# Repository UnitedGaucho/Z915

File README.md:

# Z915

An nRF52840 (MDBT50Q) wireless mechanical keyboard that fits in the chassis and recreates the functions of the Logitech G915. ZMK is used as the firmware.
G915 features to be recreated
  - Per-key RGB LED
  - Volume scroll wheel
  - Wireless (BLE)
  - Battery level reporting

Features to be added/upgraded
  - USB-C charging (G915 has micro-B USB)
  - Upgrade the feel of the rubber dome switches by using snap dome switches underneath the rubber
  - ZMK-included features

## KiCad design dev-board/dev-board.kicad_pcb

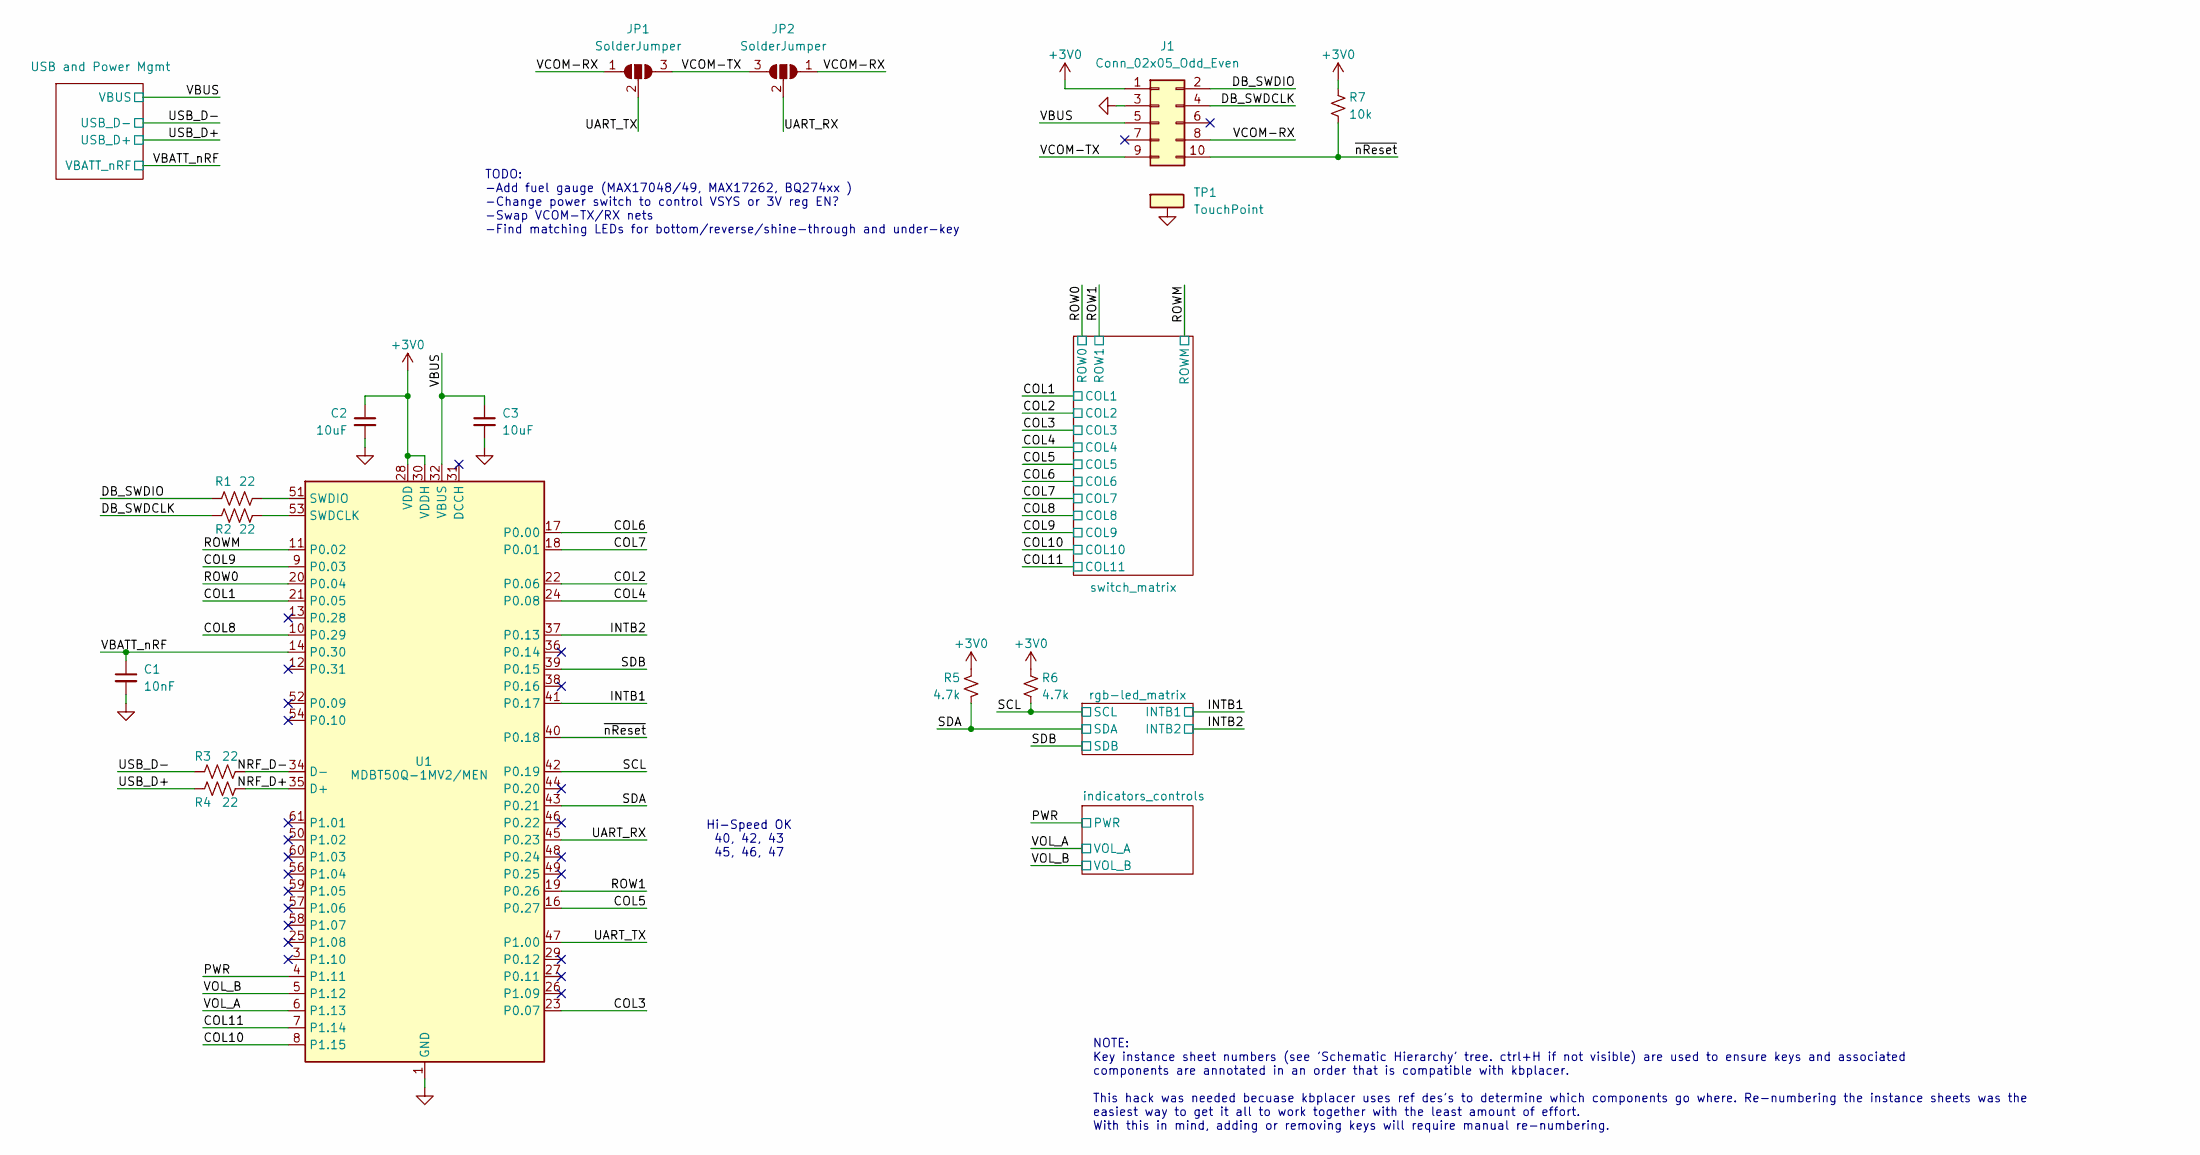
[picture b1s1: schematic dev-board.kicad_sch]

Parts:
C1: 10nF; C_0603_1608Metric
C2, C3: 10uF; C_1206_3216Metric
J1: Conn_02x05_Odd_Even; Tag-Connect_TC2050-IDC-FP_2x05_P1.27mm_Vertical
JP1, JP2: SolderJumper; SolderJumper-3_P1.3mm_Open_RoundedPad1.0x1.5mm
R1, R2, R3, R4: 22; R_0402_1005Metric
R5, R6: 4.7k; R_0402_1005Metric
R7: 10k; R_0402_1005Metric
TP1: TouchPoint; TestPoint_Pad_4.0x4.0mm
U1: MDBT50Q-1MV2/MEN; Raytac_MDBT50Q

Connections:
+3V0: C2.1, J1.1, R5.2, R6.2, R7.2, U1.28 (VDD), U1.30 (VDDH); also elsewhere on the board
/COL1: U1.21 (P0.05); also elsewhere on the board
/COL2: U1.22 (P0.06); also elsewhere on the board
/COL3: U1.23 (P0.07); also elsewhere on the board
/COL4: U1.24 (P0.08); also elsewhere on the board
/COL5: U1.16 (P0.27); also elsewhere on the board
/COL6: U1.17 (P0.00); also elsewhere on the board
/COL7: U1.18 (P0.01); also elsewhere on the board
/COL8: U1.10 (P0.29); also elsewhere on the board
/COL9: U1.9 (P0.03); also elsewhere on the board
/COL10: U1.8 (P1.15); also elsewhere on the board
/COL11: U1.7 (P1.14); also elsewhere on the board
/DB_SWDCLK: J1.4, R2.1
/DB_SWDIO: J1.2, R1.1
/INTB1: U1.41 (P0.17); also elsewhere on the board
/INTB2: U1.37 (P0.13); also elsewhere on the board
/NRF_D+: R4.2, U1.35 (D+)
/NRF_D-: R3.2, U1.34 (D-)
/PWR: U1.4 (P1.11); also elsewhere on the board
/ROW0: U1.20 (P0.04); also elsewhere on the board
/ROW1: U1.19 (P0.26); also elsewhere on the board
/ROWM: U1.11 (P0.02); also elsewhere on the board
/SCL: R6.1, U1.42 (P0.19); also elsewhere on the board
/SDA: R5.1, U1.43 (P0.21); also elsewhere on the board
/SDB: U1.39 (P0.15); also elsewhere on the board
/UART_RX: JP2.2 (C), U1.45 (P0.23)
/UART_TX: JP1.2 (C), U1.47 (P1.00)
/USB_D+: R4.1; also elsewhere on the board
/USB_D-: R3.1; also elsewhere on the board
/VBATT_nRF: C1.1, U1.14 (P0.30); also elsewhere on the board
/VBUS: C3.1, J1.5, U1.32 (VBUS); also elsewhere on the board
/VCOM-RX: J1.8, JP1.1 (A), JP2.1 (A)
/VCOM-TX: J1.9, JP1.3 (B), JP2.3 (B)
/VOL_A: U1.6 (P1.13); also elsewhere on the board
/VOL_B: U1.5 (P1.12); also elsewhere on the board
/~nReset: J1.10, R7.1, U1.40 (P0.18)
GND: C1.2, C2.2, C3.2, J1.3, TP1.1, U1.1 (GND), U1.2 (GND), U1.15 (GND), U1.33 (GND), U1.55 (GND); also elsewhere on the board
unnamed: R2.2, U1.53 (SWDCLK)
unnamed: R1.2, U1.51 (SWDIO)

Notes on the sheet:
NOTE: Key instance sheet numbers (see 'Schematic Hierarchy' tree. ctrl+H if not visible) are used to ensure keys and associated components are annotated in an order that is compatible with kbplacer. This hack was needed becuase kbplacer uses ref des's to determine which components go where. Re-numb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
Hi-Speed OK 40, 42, 43 45, 46, 47
TODO: -Add fuel gauge (MAX17048/49, MAX17262, BQ274xx ) -Change power switch to control VSYS or 3V reg EN? -Swap VCOM-TX/RX nets -Find matching LEDs for bottom/reverse/shine-through and under-key

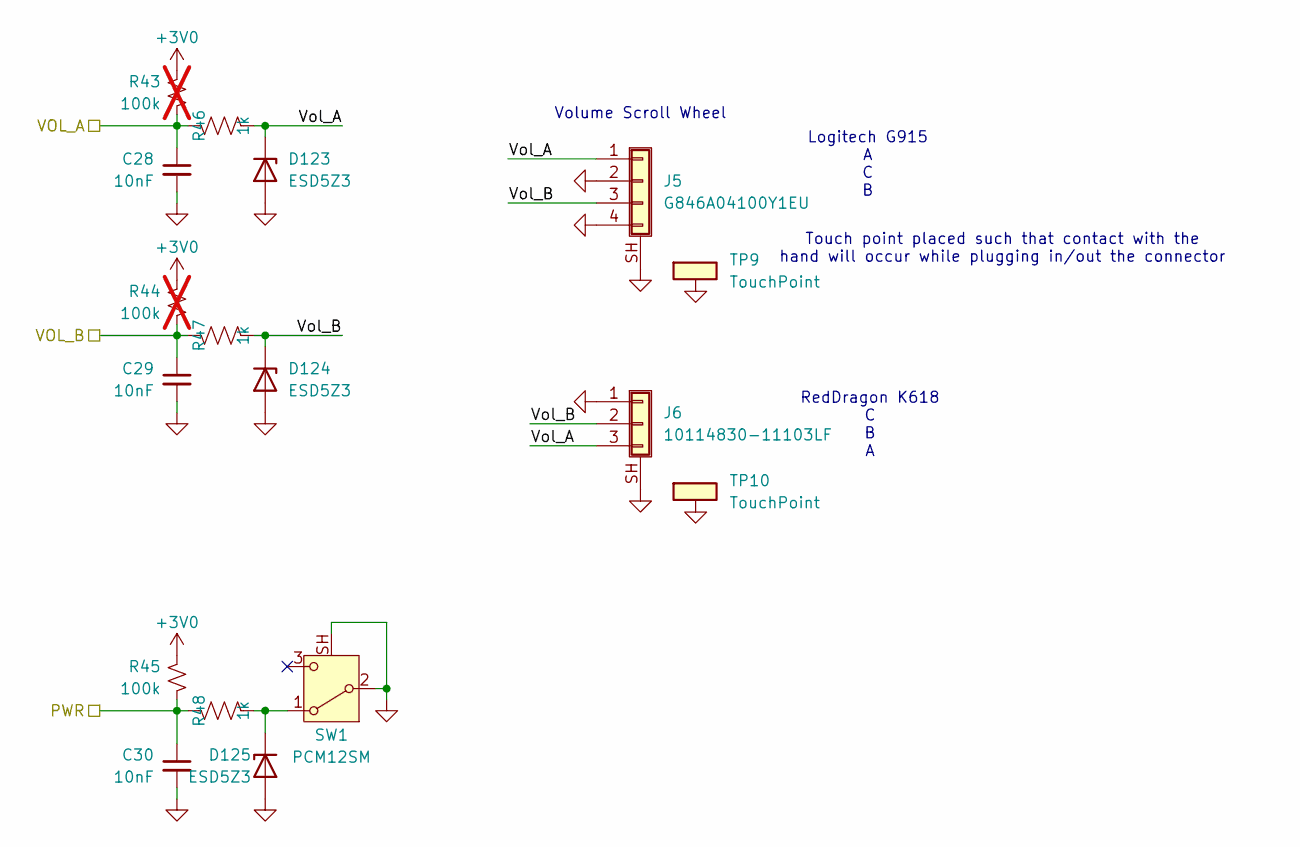
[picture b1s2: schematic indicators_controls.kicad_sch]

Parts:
C28, C29, C30: 10nF; C_0603_1608Metric
D123, D124, D125: ESD5Z3; D_SOD-523
J5: G846A04100Y1EU; AMPHENOL_G846A04100Y1EU
J6: 10114830-11103LF; AMPHENOL_10114830-11103LF
R43, R44: 100k; R_0402_1005Metric; not fitted
R45: 100k; R_0402_1005Metric
R46, R47, R48: 1k; R_0402_1005Metric
SW1: PCM12SM; SW_PCM12SMTR
TP9, TP10: TouchPoint; TestPoint_Pad_4.0x4.0mm

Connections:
+3V0: R43.2, R44.2, R45.2; also elsewhere on the board
/PWR: C30.1, R45.1, R48.1; also elsewhere on the board
/VOL_A: C28.1, R43.1, R46.1; also elsewhere on the board
/VOL_B: C29.1, R44.1, R47.1; also elsewhere on the board
/indicators_controls/Vol_A: D123.1 (K), J5.1, J6.3, R46.2
/indicators_controls/Vol_B: D124.1 (K), J5.3, J6.2, R47.2
GND: C28.2, C29.2, C30.2, D123.2 (A), D124.2 (A), D125.2 (A), J5.2, J5.4, J5.SH (Shield), J6.1, J6.SH (Shield), SW1.2 (B), SW1.SH, TP9.1, TP10.1; also elsewhere on the board
unnamed: D125.1 (K), R48.2, SW1.1 (A)

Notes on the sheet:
Logitech G915 A C B
Touch point placed such that contact with the hand will occur while plugging in/out the connector
RedDragon K618 C B A
Volume Scroll Wheel

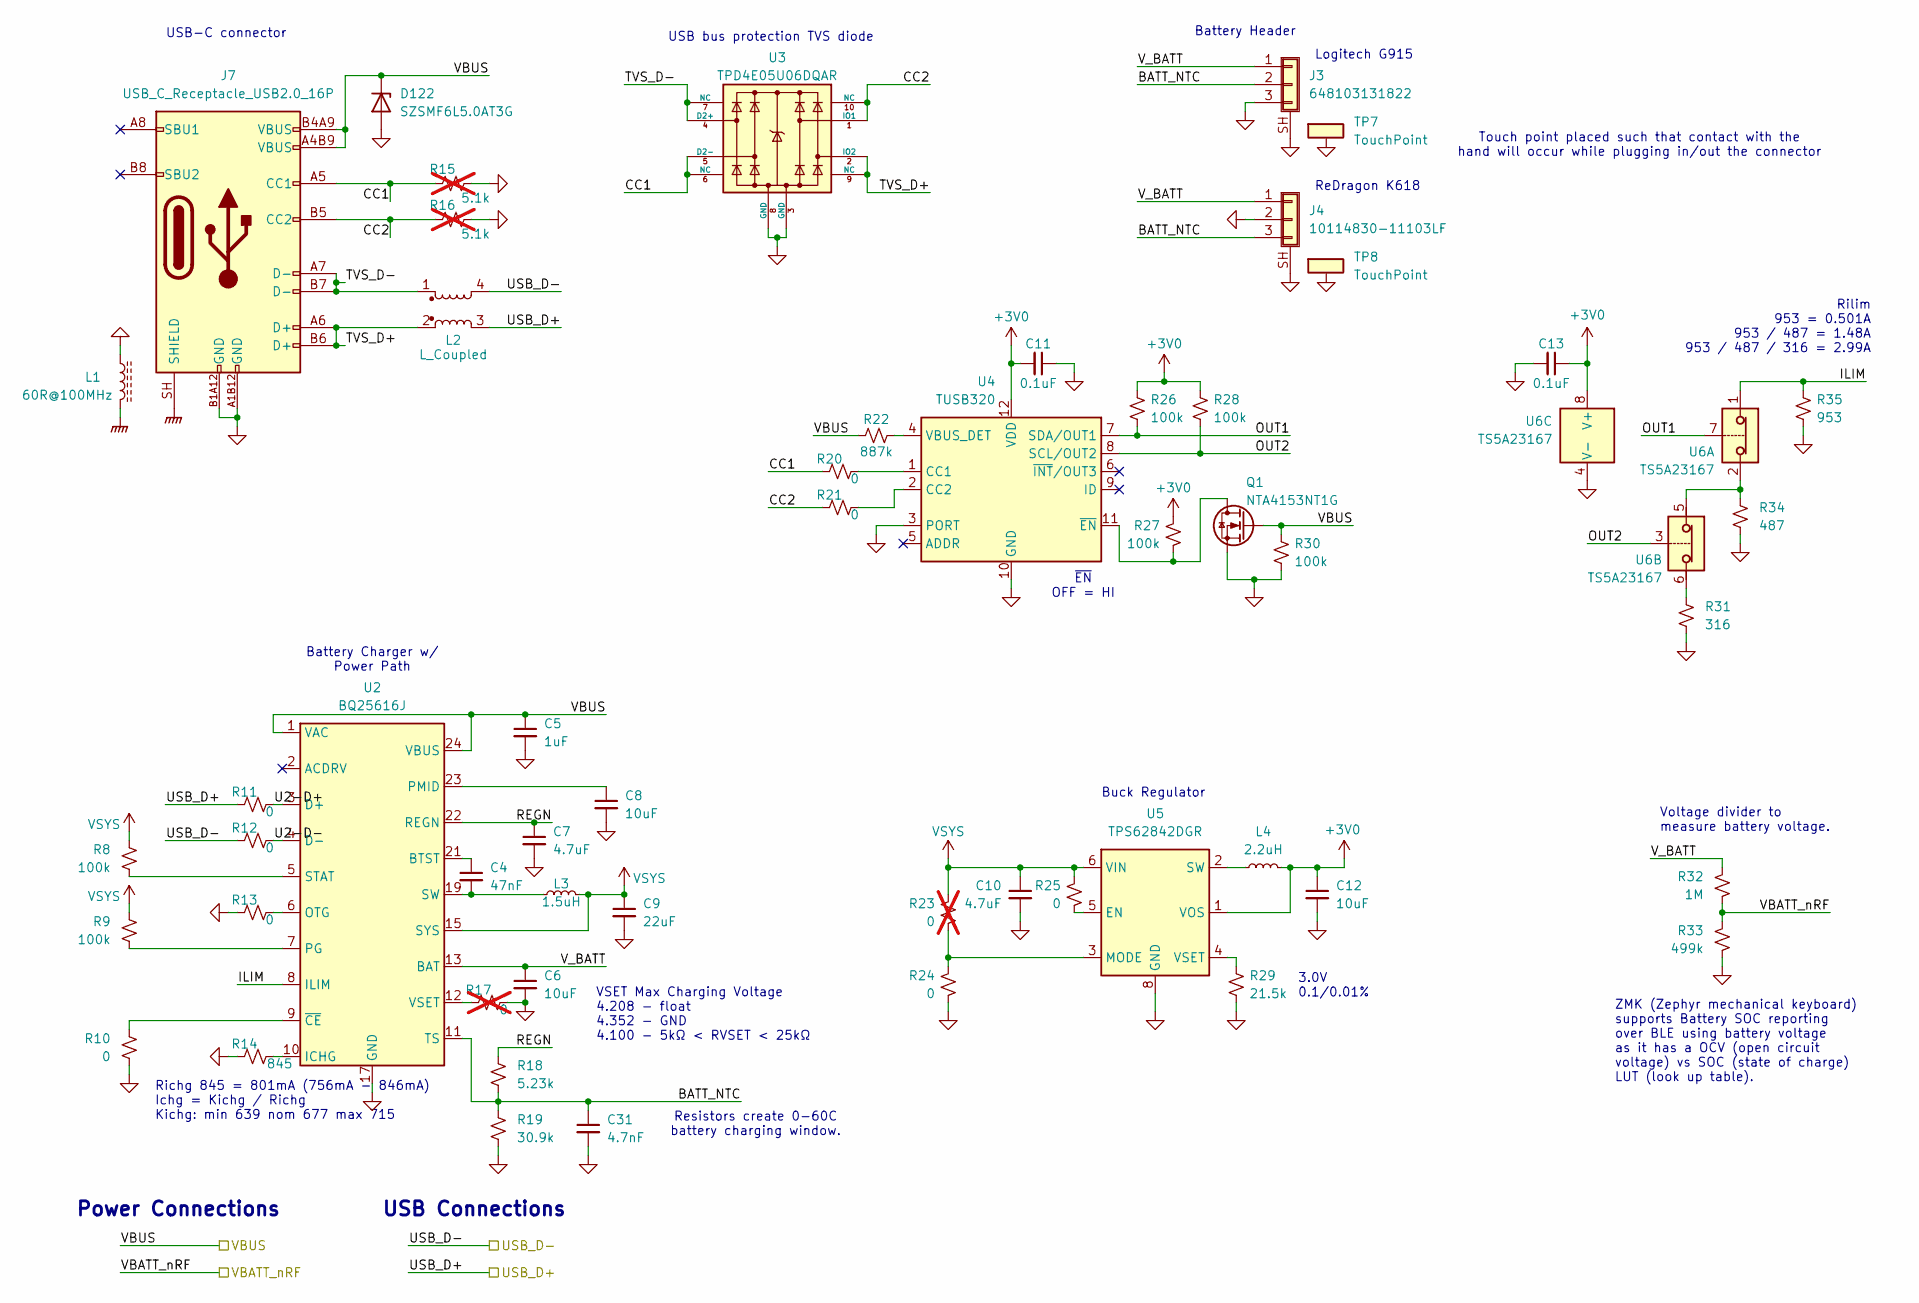
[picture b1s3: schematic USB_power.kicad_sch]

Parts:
C4: 47nF; C_0402_1005Metric
C5: 1uF; C_0603_1608Metric
C6, C8: 10uF; C_0805_2012Metric
C7: 4.7uF; C_0402_1005Metric
C9: 22uF; C_0805_2012Metric
C10: 4.7uF; C_0805_2012Metric
C11, C13: 0.1uF; C_0402_1005Metric
C12: 10uF; C_0402_1005Metric
C31: 4.7nF; C_0402_1005Metric
D122: SZSMF6L5.0AT3G; D_SOD-123F
J3: 648103131822
J4: 10114830-11103LF; AMPHENOL_10114830-11103LF
J7: USB_C_Receptacle_USB2.0_16P; AMPHENOL_12402012E212A
L1: 60R@100MHz; L_0603_1608Metric
L2: L_Coupled; FIL_ACM2012-900-2P-T001
L3: 1.5uH; L_1008_2520Metric
L4: 2.2uH; L_Murata_DFE201610P
Q1: NTA4153NT1G; SOT-416
R8, R9, R26, R27, R28, R30: 100k; R_0402_1005Metric
R10, R11, R12, R13, R20, R21, R24, R25: 0; R_0402_1005Metric
R14: 845; R_0402_1005Metric
R15, R16: 5.1k; R_0402_1005Metric; not fitted
R17, R23: 0; R_0402_1005Metric; not fitted
R18: 5.23k; R_0402_1005Metric
R19: 30.9k; R_0402_1005Metric
R22: 887k; R_0402_1005Metric
R29: 21.5k; R_0402_1005Metric
R31: 316; R_0402_1005Metric
R32: 1M; R_0402_1005Metric
R33: 499k; R_0402_1005Metric
R34: 487; R_0402_1005Metric
R35: 953; R_0402_1005Metric
TP7, TP8: TouchPoint; TestPoint_Pad_4.0x4.0mm
U2: BQ25616J; Texas_RTW_WQFN-24-1EP_4x4mm_P0.5mm_EP2.7x2.7mm_ThermalVias
U3: TPD4E05U06DQAR; USON-10
U4: TUSB320; Texas_X2QFN-12_1.6x1.6mm_P0.4mm
U5: TPS62842DGR; HVSSOP-8-1EP_3x3mm_P0.65mm_EP1.57x1.89mm
U6: TS5A23167; VSSOP-8_2.3x2mm_P0.5mm

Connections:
+3V0: C11.2, C12.1, C13.1, L4.2, R26.2, R27.2, R28.2, U4.12 (VDD), U5.1 (VOS), U6.8 (V+); also elsewhere on the board
/USB and Power Mgmt/BATT_NTC: C31.1, J3.2, J4.3, R18.1, R19.2, U2.11 (TS)
/USB and Power Mgmt/CC1: J7.A5 (CC1), R15.2, R20.2, U3.5 (D2-), U3.6 (NC)
/USB and Power Mgmt/CC2: J7.B5 (CC2), R16.2, R21.2, U3.1 (IO1), U3.10 (NC)
/USB and Power Mgmt/ILIM: R35.2, U2.8 (ILIM), U6.1
/USB and Power Mgmt/OUT1: R26.1, U4.7 (SDA/OUT1), U6.7
/USB and Power Mgmt/OUT2: R28.1, U4.8 (SCL/OUT2), U6.3
/USB and Power Mgmt/REGN: C7.1, R18.2, U2.22 (REGN)
/USB and Power Mgmt/TVS_D+: J7.A6 (D+), J7.B6 (D+), L2.2, U3.2 (IO2), U3.9 (NC)
/USB and Power Mgmt/TVS_D-: J7.A7 (D-), J7.B7 (D-), L2.1, U3.4 (D2+), U3.7 (NC)
/USB and Power Mgmt/U2-D+: R11.1, U2.3 (D+)
/USB and Power Mgmt/U2-D-: R12.1, U2.4 (D-)
/USB_D+: L2.3, R11.2; also elsewhere on the board
/USB_D-: L2.4, R12.2; also elsewhere on the board
/VBATT_nRF: R32.1, R33.2; also elsewhere on the board
/VBUS: C5.1, D122.1 (K), J7.A4B9 (VBUS), J7.B4A9 (VBUS), Q1.G, R22.2, R30.2, U2.1 (VAC), U2.24 (VBUS); also elsewhere on the board
BAT: C6.1, J3.1, J4.1, R32.2, U2.13 (BAT), U2.14 (BAT)
GND: C5.2, C6.2, C7.2, C8.2, C9.2, C10.2, C11.1, C12.2, C13.2, C31.2, D122.2 (A), J3.3, J3.SH (Shield), J4.2, J4.SH (Shield), J7.A1B12 (GND), J7.B1A12 (GND), L1.1, Q1.S, R10.2, R13.2, R14.2, R15.1, R16.1, R17.1, R19.1, R24.1, R29.1, R30.1, R31.1, R33.1, R34.1, R35.1, TP7.1, TP8.1, U2.17 (GND), U2.18 (GND), U2.25 (GND), U3.3 (GND), U3.8 (GND), U4.3 (PORT), U4.10 (GND), U5.8 (GND), U5.9 (EP), U6.4 (V-); also elsewhere on the board
GNDPWR: J7.SH (SHIELD), L1.2
unnamed: C4.2, L3.1, U2.19 (SW), U2.20 (SW)
unnamed: R31.2, U6.6
unnamed: R34.2, U6.2, U6.5
unnamed: C4.1, U2.21 (BTST)
unnamed: R14.1, U2.10 (ICHG)
unnamed: R13.1, U2.6 (OTG)
unnamed: R9.2, U2.7 (PG)
unnamed: C8.1, U2.23 (PMID)
unnamed: R8.2, U2.5 (STAT)
unnamed: R17.2, U2.12 (VSET)
unnamed: R10.1, U2.9 (~CE)
unnamed: R20.1, U4.1 (CC1)
unnamed: R21.1, U4.2 (CC2)
unnamed: R22.1, U4.4 (VBUS_DET)
unnamed: Q1.D, R27.1, U4.11 (~EN)
unnamed: R25.1, U5.5 (EN)
unnamed: R23.1, R24.2, U5.3 (MODE)
unnamed: L4.1, U5.2 (SW)
unnamed: R29.2, U5.4 (VSET)
VSYS: C9.1, C10.1, L3.2, R8.1, R9.1, R23.2, R25.2, U2.15 (SYS), U2.16 (SYS), U5.6 (VIN); also elsewhere on the board

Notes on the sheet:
ReDragon K618
Resistors create 0-60C battery charging window.
Voltage divider to measure battery voltage.
Touch point placed such that contact with the hand will occur while plugging in/out the connector
Battery Charger w/ Power Path
USB bus protection TVS diode
Richg 845 = 801mA (756mA - 846mA) Ichg = Kichg / Richg Kichg: min 639 nom 677 max 715
3.0V 0.1/0.01%
USB Connections
Buck Regulator
USB-C connector
Logitech G915
ZMK (Zephyr mechanical keyboard) supports Battery SOC reporting over BLE using battery voltage as it has a OCV (open circuit voltage) vs SOC (state of charge) LUT (look up table).
Rilim 953 = 0.501A 953 / 487 = 1.48A 953 / 487 / 316 = 2.99A
VSET Max Charging Voltage 4.208 - float 4.352 - GND 4.100 - 5kΩ < RVSET < 25kΩ
Battery Header
Power Connections
~{EN} OFF = HI

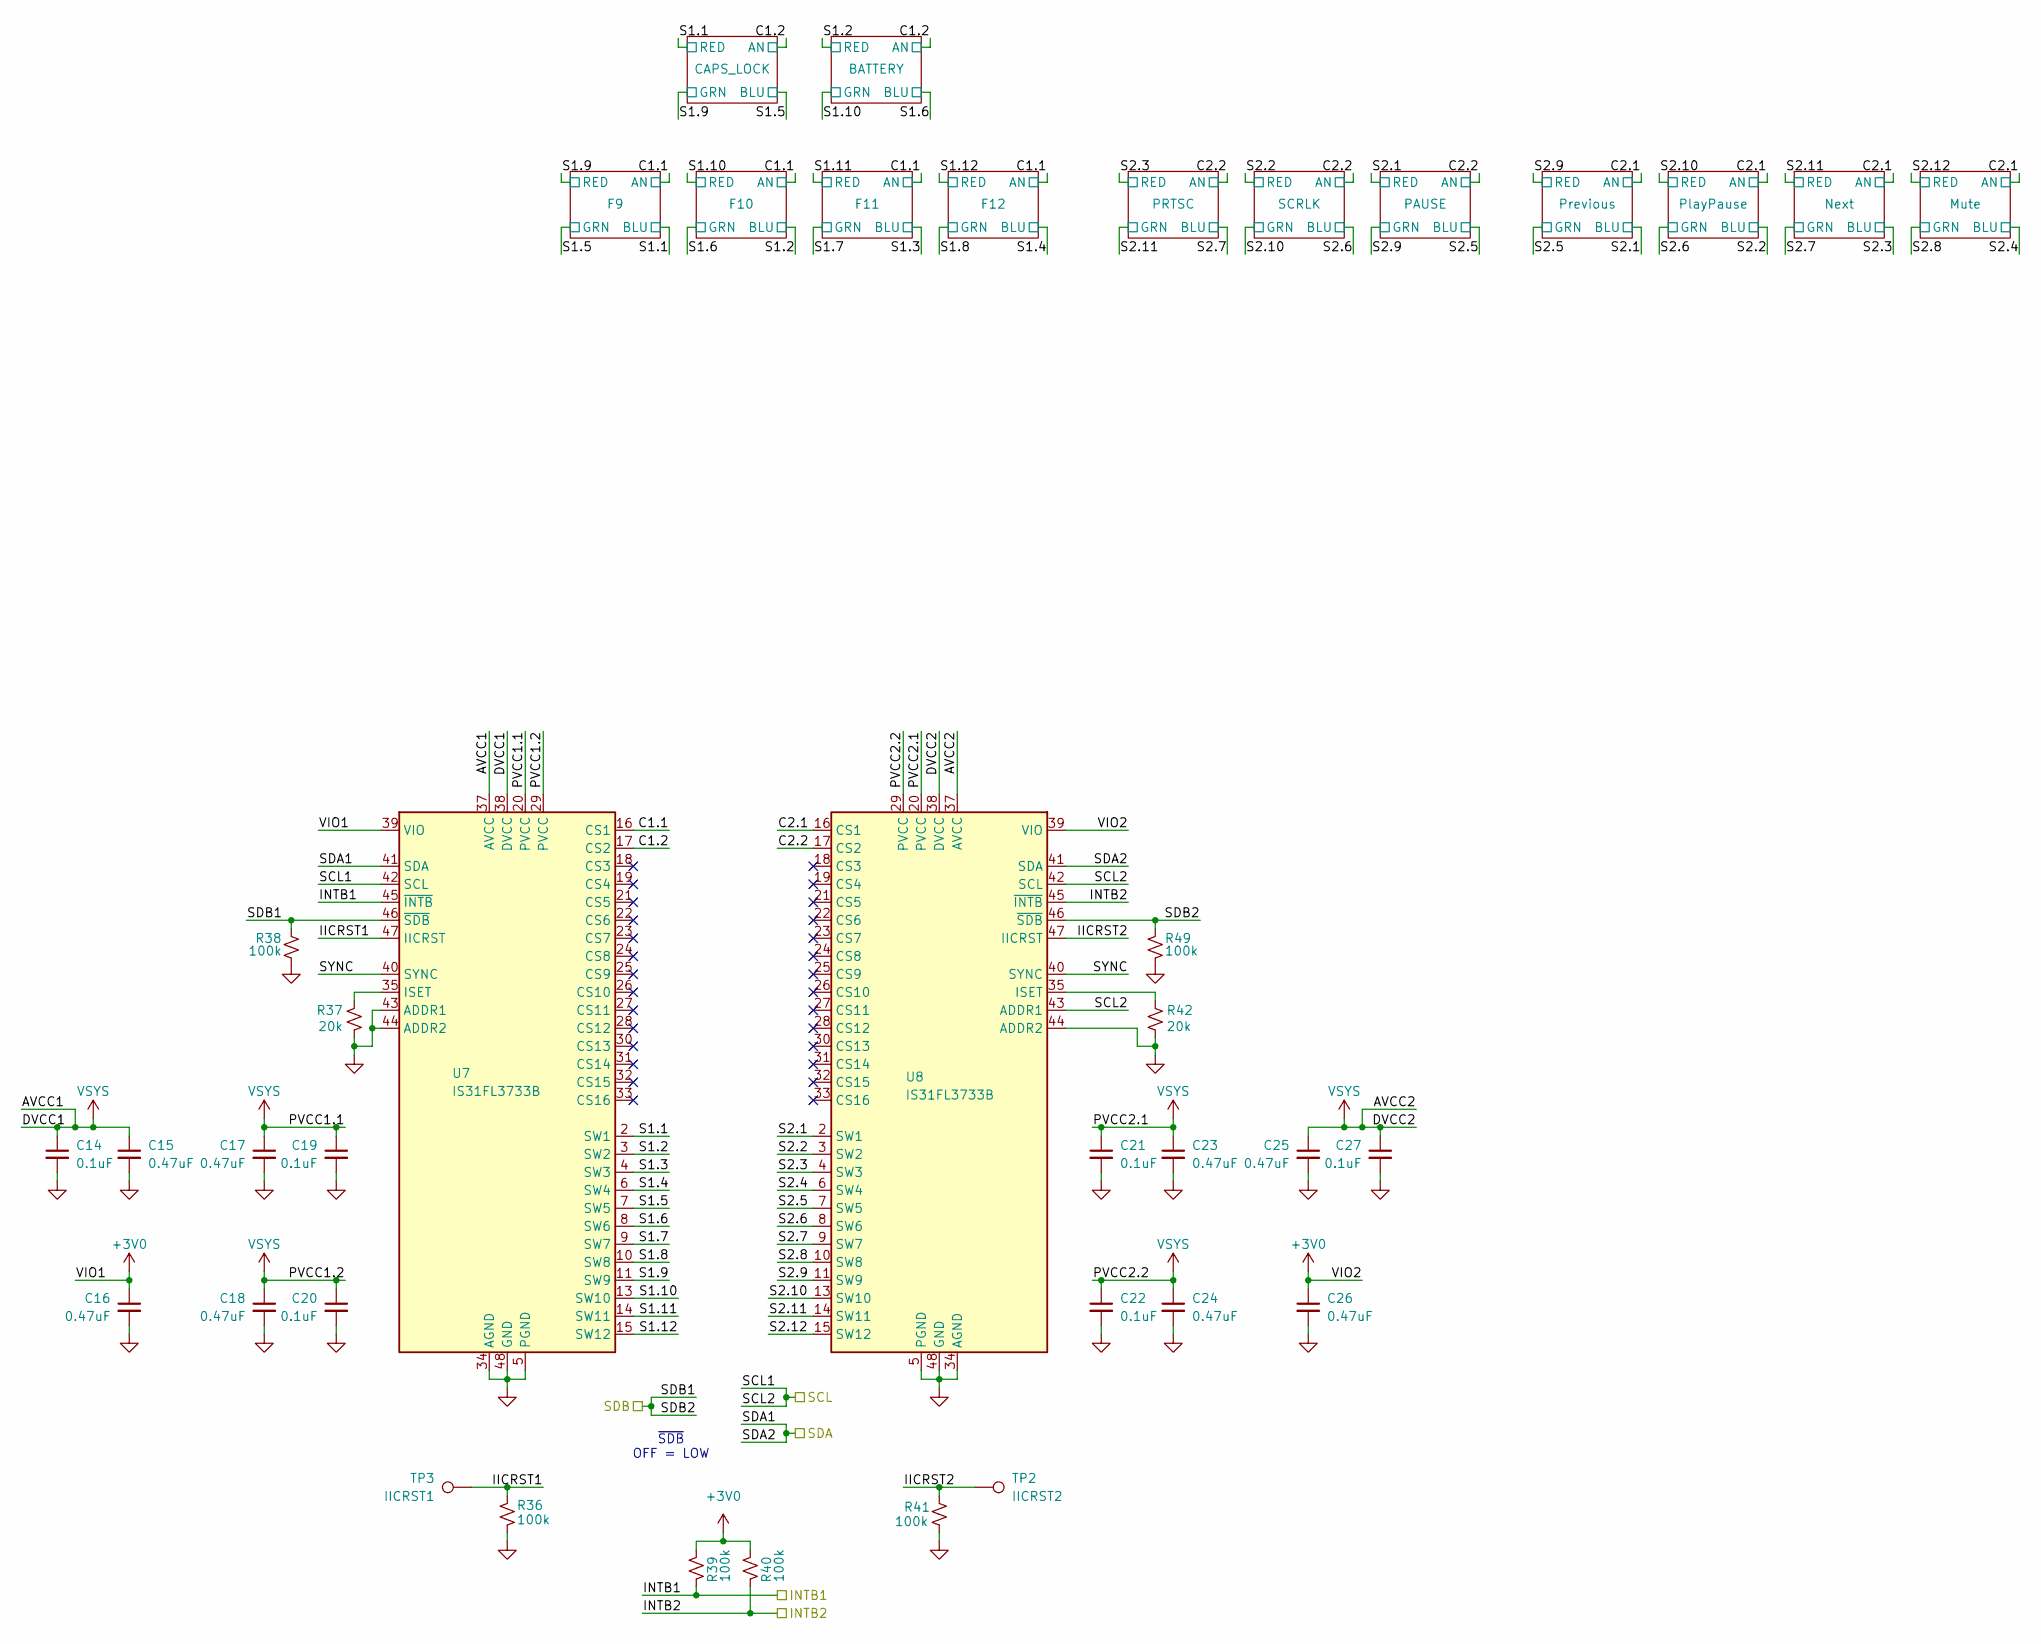
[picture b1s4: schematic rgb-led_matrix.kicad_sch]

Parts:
C14, C19, C20, C21, C22, C27: 0.1uF; C_0402_1005Metric
C15, C16, C17, C18, C23, C24, C25, C26: 0.47uF; C_0402_1005Metric
R36, R38, R39, R40, R41, R49: 100k; R_0402_1005Metric
R37, R42: 20k; R_0402_1005Metric
TP2: IICRST2; TestPoint_Pad_D1.0mm
TP3: IICRST1; TestPoint_Pad_D1.0mm
U7, U8: IS31FL3733B; TQFP-48-1EP_7x7mm_P0.5mm_EP5x5mm

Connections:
+3V0: C16.1, C26.1, R39.2, R40.2, U7.39 (VIO), U8.39 (VIO); also elsewhere on the board
/INTB1: R39.1, U7.45 (~INTB); also elsewhere on the board
/INTB2: R40.1, U8.45 (~INTB); also elsewhere on the board
/SCL: U7.42 (SCL), U8.42 (SCL), U8.43 (ADDR1); also elsewhere on the board
/SDA: U7.41 (SDA), U8.41 (SDA); also elsewhere on the board
/SDB: R38.2, R49.2, U7.46 (~SDB), U8.46 (~SDB); also elsewhere on the board
/rgb-led_matrix/C1.1: U7.16 (CS1); also elsewhere on the board
/rgb-led_matrix/C1.2: U7.17 (CS2); also elsewhere on the board
/rgb-led_matrix/C2.1: U8.16 (CS1); also elsewhere on the board
/rgb-led_matrix/C2.2: U8.17 (CS2); also elsewhere on the board
/rgb-led_matrix/IICRST1: R36.2, TP3.1 (1_1), U7.47 (IICRST)
/rgb-led_matrix/IICRST2: R41.1, TP2.1 (1_1), U8.47 (IICRST)
/rgb-led_matrix/S1.1: U7.2 (SW1); also elsewhere on the board
/rgb-led_matrix/S1.2: U7.3 (SW2); also elsewhere on the board
/rgb-led_matrix/S1.3: U7.4 (SW3); also elsewhere on the board
/rgb-led_matrix/S1.4: U7.6 (SW4); also elsewhere on the board
/rgb-led_matrix/S1.5: U7.7 (SW5); also elsewhere on the board
/rgb-led_matrix/S1.6: U7.8 (SW6); also elsewhere on the board
/rgb-led_matrix/S1.7: U7.9 (SW7); also elsewhere on the board
/rgb-led_matrix/S1.8: U7.10 (SW8); also elsewhere on the board
/rgb-led_matrix/S1.9: U7.11 (SW9); also elsewhere on the board
/rgb-led_matrix/S1.10: U7.13 (SW10); also elsewhere on the board
/rgb-led_matrix/S1.11: U7.14 (SW11); also elsewhere on the board
/rgb-led_matrix/S1.12: U7.15 (SW12); also elsewhere on the board
/rgb-led_matrix/S2.1: U8.2 (SW1); also elsewhere on the board
/rgb-led_matrix/S2.2: U8.3 (SW2); also elsewhere on the board
/rgb-led_matrix/S2.3: U8.4 (SW3); also elsewhere on the board
/rgb-led_matrix/S2.4: U8.6 (SW4); also elsewhere on the board
/rgb-led_matrix/S2.5: U8.7 (SW5); also elsewhere on the board
/rgb-led_matrix/S2.6: U8.8 (SW6); also elsewhere on the board
/rgb-led_matrix/S2.7: U8.9 (SW7); also elsewhere on the board
/rgb-led_matrix/S2.8: U8.10 (SW8); also elsewhere on the board
/rgb-led_matrix/S2.9: U8.11 (SW9); also elsewhere on the board
/rgb-led_matrix/S2.10: U8.13 (SW10); also elsewhere on the board
/rgb-led_matrix/S2.11: U8.14 (SW11); also elsewhere on the board
/rgb-led_matrix/S2.12: U8.15 (SW12); also elsewhere on the board
/rgb-led_matrix/SYNC: U7.40 (SYNC), U8.40 (SYNC)
GND: C14.2, C15.2, C16.2, C17.2, C18.2, C19.2, C20.2, C21.2, C22.2, C23.2, C24.2, C25.2, C26.2, C27.2, R36.1, R37.2, R38.1, R41.2, R42.2, R49.1, U7.5 (PGND), U7.12 (PGND), U7.34 (AGND), U7.43 (ADDR1), U7.44 (ADDR2), U7.48 (GND), U7.49 (GND), U8.5 (PGND), U8.12 (PGND), U8.34 (AGND), U8.44 (ADDR2), U8.48 (GND), U8.49 (GND); also elsewhere on the board
unnamed: R37.1, U7.35 (ISET)
unnamed: R42.1, U8.35 (ISET)
VSYS: C14.1, C15.1, C17.1, C18.1, C19.1, C20.1, C21.1, C22.1, C23.1, C24.1, C25.1, C27.1, U7.20 (PVCC), U7.29 (PVCC), U7.37 (AVCC), U7.38 (DVCC), U8.20 (PVCC), U8.29 (PVCC), U8.37 (AVCC), U8.38 (DVCC); also elsewhere on the board

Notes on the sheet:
~{SDB} OFF = LOW

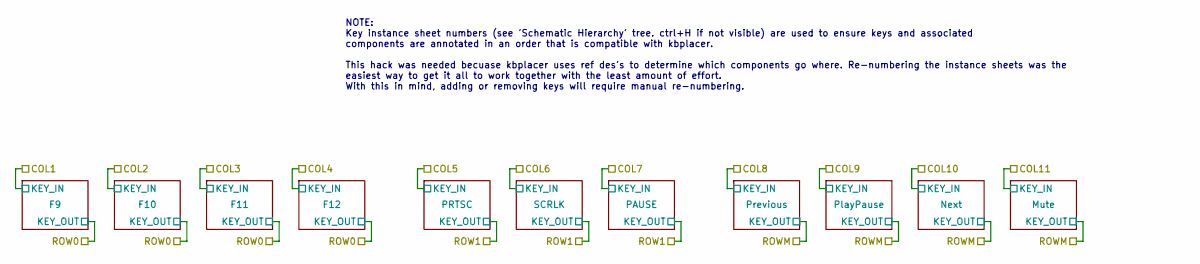
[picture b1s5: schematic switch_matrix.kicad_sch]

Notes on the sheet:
NOTE: Key instance sheet numbers (see 'Schematic Hierarchy' tree. ctrl+H if not visible) are used to ensure keys and associated components are annotated in an order that is compatible with kbplacer. This hack was needed becuase kbplacer uses ref des's to determine which components go where. Re-numb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

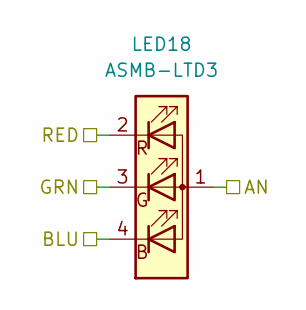
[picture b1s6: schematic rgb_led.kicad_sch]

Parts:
LED18: ASMB-LTD3; LED_ASMB-LTD3

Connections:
/rgb-led_matrix/C1.1: LED18.1 (A); also elsewhere on the board
/rgb-led_matrix/S1.1: LED18.4 (BK); also elsewhere on the board
/rgb-led_matrix/S1.5: LED18.3 (GK); also elsewhere on the board
/rgb-led_matrix/S1.9: LED18.2 (RK); also elsewhere on the board

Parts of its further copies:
LED19, LED20, LED21, LED22, LED23, LED24, LED122, LED123: ASMB-LTD3; LED_ASMB-LTD3

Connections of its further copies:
/rgb-led_matrix/C1.1: LED19.1 (A), LED20.1 (A), LED21.1 (A); also elsewhere on the board
/rgb-led_matrix/C1.2: LED122.1 (A), LED123.1 (A); also elsewhere on the board
/rgb-led_matrix/C2.2: LED22.1 (A), LED23.1 (A), LED24.1 (A); also elsewhere on the board
/rgb-led_matrix/S1.1: LED122.2 (RK); also elsewhere on the board
/rgb-led_matrix/S1.2: LED19.4 (BK), LED123.2 (RK); also elsewhere on the board
/rgb-led_matrix/S1.3: LED20.4 (BK); also elsewhere on the board
/rgb-led_matrix/S1.4: LED21.4 (BK); also elsewhere on the board
/rgb-led_matrix/S1.5: LED122.4 (BK); also elsewhere on the board
/rgb-led_matrix/S1.6: LED19.3 (GK), LED123.4 (BK); also elsewhere on the board
/rgb-led_matrix/S1.7: LED20.3 (GK); also elsewhere on the board
/rgb-led_matrix/S1.8: LED21.3 (GK); also elsewhere on the board
/rgb-led_matrix/S1.9: LED122.3 (GK); also elsewhere on the board
/rgb-led_matrix/S1.10: LED19.2 (RK), LED123.3 (GK); also elsewhere on the board
/rgb-led_matrix/S1.11: LED20.2 (RK); also elsewhere on the board
/rgb-led_matrix/S1.12: LED21.2 (RK); also elsewhere on the board
/rgb-led_matrix/S2.1: LED24.2 (RK); also elsewhere on the board
/rgb-led_matrix/S2.2: LED23.2 (RK); also elsewhere on the board
/rgb-led_matrix/S2.3: LED22.2 (RK); also elsewhere on the board
/rgb-led_matrix/S2.5: LED24.4 (BK); also elsewhere on the board
/rgb-led_matrix/S2.6: LED23.4 (BK); also elsewhere on the board
/rgb-led_matrix/S2.7: LED22.4 (BK); also elsewhere on the board
/rgb-led_matrix/S2.9: LED24.3 (GK); also elsewhere on the board
/rgb-led_matrix/S2.10: LED23.3 (GK); also elsewhere on the board
/rgb-led_matrix/S2.11: LED22.3 (GK); also elsewhere on the board

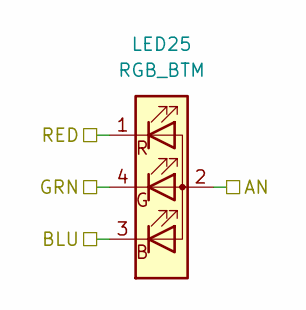
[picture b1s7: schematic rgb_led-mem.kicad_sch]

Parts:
LED25: RGB_BTM; LED_XZMDKCBDDG45S-9

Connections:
/rgb-led_matrix/C2.1: LED25.2 (A); also elsewhere on the board
/rgb-led_matrix/S2.1: LED25.3 (BK); also elsewhere on the board
/rgb-led_matrix/S2.5: LED25.4 (GK); also elsewhere on the board
/rgb-led_matrix/S2.9: LED25.1 (RK); also elsewhere on the board

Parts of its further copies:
LED26: RGB_BTM; LED_XZMDKCBDDG45S-9

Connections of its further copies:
/rgb-led_matrix/C2.1: LED26.2 (A); also elsewhere on the board
/rgb-led_matrix/S2.2: LED26.3 (BK); also elsewhere on the board
/rgb-led_matrix/S2.6: LED26.4 (GK); also elsewhere on the board
/rgb-led_matrix/S2.10: LED26.1 (RK); also elsewhere on the board

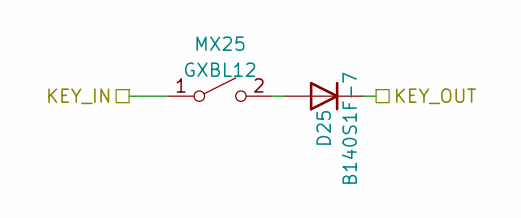
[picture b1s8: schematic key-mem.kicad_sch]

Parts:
D25: B140S1F-7; D_SOD-123F
MX25: GXBL12; SW_GXBL12450

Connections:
/COL8: MX25.1 (A); also elsewhere on the board
/ROWM: D25.1 (K); also elsewhere on the board
unnamed: D25.2 (A), MX25.2 (B)

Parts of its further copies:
D26, D27, D28: B140S1F-7; D_SOD-123F
MX26, MX27, MX28: GXBL12; SW_GXBL12450

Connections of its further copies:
/COL9: MX26.1 (A); also elsewhere on the board
/COL10: MX27.1 (A); also elsewhere on the board
/COL11: MX28.1 (A); also elsewhere on the board
/ROWM: D26.1 (K), D27.1 (K), D28.1 (K); also elsewhere on the board
unnamed: D26.2 (A), MX26.2 (B)
unnamed: D27.2 (A), MX27.2 (B)
unnamed: D28.2 (A), MX28.2 (B)

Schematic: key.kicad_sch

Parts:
D18: B140S1F-7; D_SOD-123F
MX18: 1.00u; SW_Kailh_Choc_V1_THT

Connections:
/COL1: MX18.2 (B); also elsewhere on the board
/ROW0: D18.1 (K); also elsewhere on the board
unnamed: D18.2 (A), MX18.1 (A)

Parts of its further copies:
D19, D20, D21, D22, D23, D24: B140S1F-7; D_SOD-123F
MX19, MX20, MX21, MX22, MX23, MX24: 1.00u; SW_Kailh_Choc_V1_THT

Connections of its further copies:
/COL2: MX19.2 (B); also elsewhere on the board
/COL3: MX20.2 (B); also elsewhere on the board
/COL4: MX21.2 (B); also elsewhere on the board
/COL5: MX22.2 (B); also elsewhere on the board
/COL6: MX23.2 (B); also elsewhere on the board
/COL7: MX24.2 (B); also elsewhere on the board
/ROW0: D19.1 (K), D20.1 (K), D21.1 (K); also elsewhere on the board
/ROW1: D22.1 (K), D23.1 (K), D24.1 (K); also elsewhere on the board
unnamed: D19.2 (A), MX19.1 (A)
unnamed: D20.2 (A), MX20.1 (A)
unnamed: D21.2 (A), MX21.1 (A)
unnamed: D22.2 (A), MX22.1 (A)
unnamed: D23.2 (A), MX23.1 (A)
unnamed: D24.2 (A), MX24.1 (A)

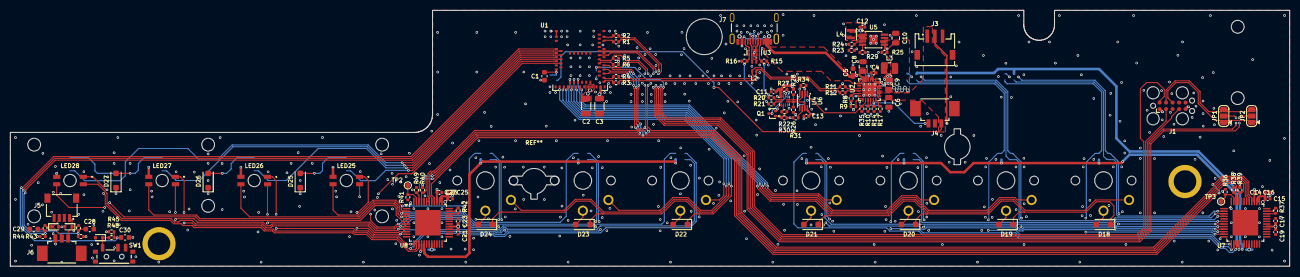
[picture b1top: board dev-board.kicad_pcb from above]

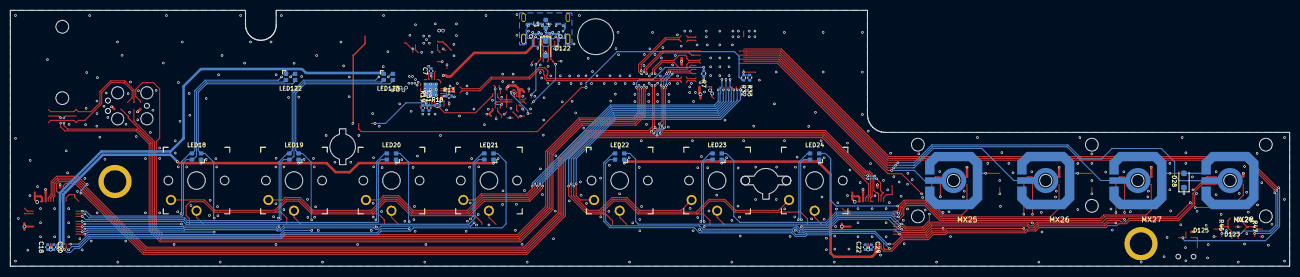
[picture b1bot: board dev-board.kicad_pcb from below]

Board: 4 copper layers, 250.0 x 50.0 mm, 143 parts (35 on the bottom side), 119 nets.

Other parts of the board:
LED27, LED28: RGB_BTM; LED_XZMDKCBDDG45S-9

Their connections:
/rgb-led_matrix/C2.1: LED27.2 (A), LED28.2 (A); also elsewhere on the board
/rgb-led_matrix/S2.3: LED27.3 (BK); also elsewhere on the board
/rgb-led_matrix/S2.4: LED28.3 (BK); also elsewhere on the board
/rgb-led_matrix/S2.7: LED27.4 (GK); also elsewhere on the board
/rgb-led_matrix/S2.8: LED28.4 (GK); also elsewhere on the board
/rgb-led_matrix/S2.11: LED27.1 (RK); also elsewhere on the board
/rgb-led_matrix/S2.12: LED28.1 (RK); also elsewhere on the board
